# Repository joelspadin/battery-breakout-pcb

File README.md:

# Battery Breakout PCB

This is a small PCB for connecting various types of 2-pin LiPo batteries. It has connectors for Molex Pico EZ-mate, JST SH, and JST PH plugs as well as a terminal for bare wire batteries. It also has a 2-pin header for connecting to a device.

Because there is no standard polarity for these batteries, the pins are not labeled as positive and negative. Instead, the pins on the left side of each connector are labeled 1 and are connected together, and the pins on the right side of each connector are labeled 2 and are connected together. You should check the polarity of the battery before connecting the breakout to your device. For example, if the positive wire of the battery is on the 1 (left) side of the connector, you should connect the positive side of your device to the 1 (left) side of the 2-pin header.

## Bill of Materials

You will need one of each of the following parts:

- 2-pin header, 2.54 mm pitch
- 2-pin terminal block, 3.5 mm pitch
  - e.g. Phoenix Contact 1935161
- JST B2B-PH-K-S
- JST BM02B-SRSS-TB
- Molex 0781710002

## Enclosure

A 3D-printable enclosure is also provided in [STEP](enclosure/battery-breakout-enclosure.step) and [3MF](enclosure/battery-breakout-enclosure.3mf) formats. This covers the bottom of the PCB to prevent the through hole components from shorting out on anything.

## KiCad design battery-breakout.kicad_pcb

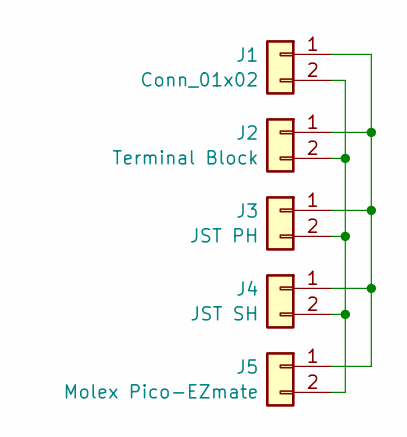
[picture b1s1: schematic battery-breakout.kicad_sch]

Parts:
J1: Conn_01x02; PinHeader_1x02_P2.54mm_Vertical
J2: Terminal Block; TerminalBlock_Phoenix_PT-1,5-2-3.5-H_1x02_P3.50mm_Horizontal
J3: JST PH; JST_PH_B2B-PH-K_1x02_P2.00mm_Vertical
J4: JST SH; JST_SH_BM02B-SRSS-TB_1x02-1MP_P1.00mm_Vertical
J5: Molex Pico-EZmate; Molex_Pico-EZmate_78171-0002_1x02-1MP_P1.20mm_Vertical

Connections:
unnamed: J1.1, J2.1, J3.1, J4.1, J5.1
unnamed: J1.2, J2.2, J3.2, J4.2, J5.2

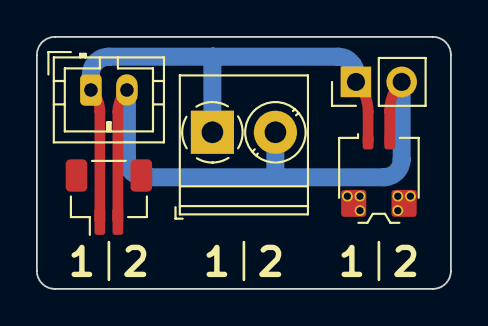
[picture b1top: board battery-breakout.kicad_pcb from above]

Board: 2 copper layers, 23.0 x 14.0 mm, 5 parts (0 on the bottom side), 2 nets.

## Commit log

2024-01-06 Add documentation and 3D models
